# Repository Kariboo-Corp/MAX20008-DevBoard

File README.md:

This repo contains my work on the MAX20008 buck converter. The *Gerbers* folder contains the fabrication outputs, the *BOM+CPL* folder contains the BOM and CPL. 

## Component Dimensioning & Notes on PCB design

## Power supply : MAX 20008 

 In the board dimensioning file from the V1 MUAV Board I estimated that the eventual current draw of the MUAV board would be at least 6A (generous estimate).  I chose the MAX20008 buck converter, rated for 8A RMS. Here i detail the steps i took to dimension the different components . 

### RFOSC : 

using a Lower Fosc = lower temp increase, i chose fosc = 250Khz

with Fosc in kHz and Rosc in kohm 

We choose FOSC = 250kHz , RFOSC= 120 kohm soit 110kohm (E96) -> fosc = 243kHz

### power inductor 

Lmin1: we take Vin = 22.2V (nominal batt voltage)
m=0,15
Lmin1 = 6.5µH \\
Lmin2 = 11.1µH \\
Lmin = 6.5µH \\
Lmax = 6.8µH \\ 

we choose Lnom = 8.2µH, IMAX =8A, ISAT = 10A  : SRP1265C-100M : ISAT = 20A, Irms = 12A, L =10µF (no 8.2 µH available at this time)

### Input capacitor : 

Cin = 4.7µF minimum, capacitors used :GRT188R6YA475KE13 , LCSC part nb : C711100
Cbyp = 100nF, GRT188R6YA475KE13 type from murata , LCSC part nb : C85960

Celec = 47µF,  nichicon low esr 250mohm, LCSC part nb: C473201 

Iload(max) = 8A tehrefore Irms = 4A . Input cap should exhibit less than 10°c rise in temp at rms input current

Use low ESR cap 

### Output capacitor : 

we take DeltaV max = 50mV, Delta I = 2A,  fc = 10KHz 

Cout = 63µF min, we take  Cout= 100µF part nb =  GRM32ER61A107ME20L

### Compensation circuitry : 

GEA = 780µS, REA = 1.5MOhm   CHECK VALUES!!! -> DNP on PCB for now

We dimension RC = 8.8K, 
             CC = 39nF, 
             CF= 9nF 

### Reverse polarity protection: 

I added a  SB1060L schottky diode in series with Vin +, 
Forward voltage = 0. 55V , rated 10A . TO 277B package

JLCPCB part nb: C2929649

## Board Build

4 Layer board to emulate the final design's temperature caracteristics. 

The board is 50*72mm. Output is on two banana Jacks. Voltage input is on two solder/TH pads.  

Inductor current can be probed by placing a wire between these pads:

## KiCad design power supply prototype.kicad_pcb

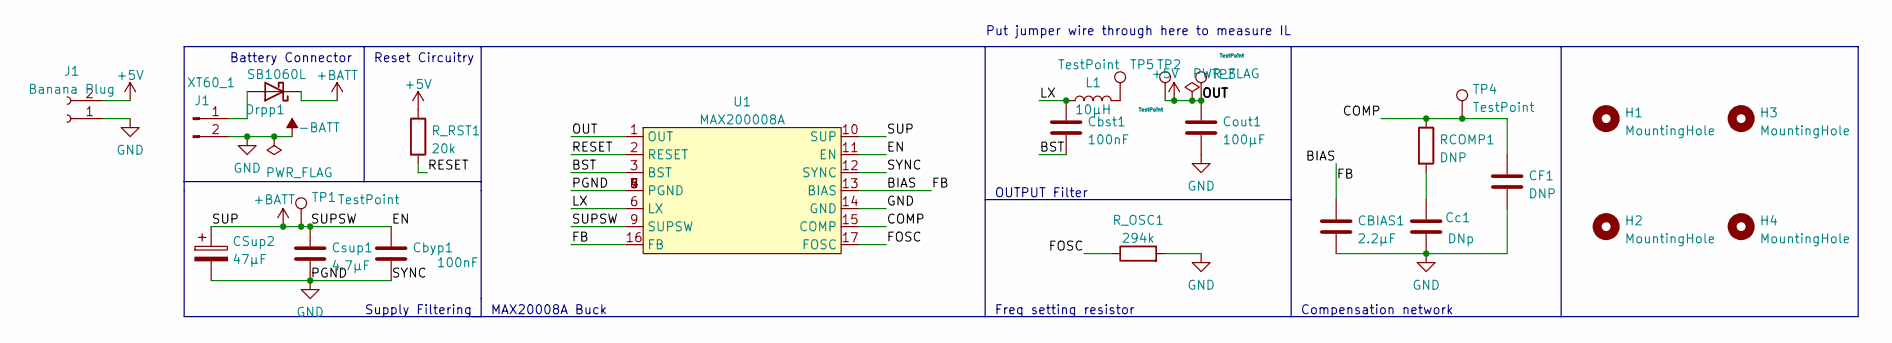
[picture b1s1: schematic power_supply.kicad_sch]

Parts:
CBIAS1: 2.2µF; C_0603_1608Metric_Pad1.08x0.95mm_HandSolder
CF1: DNP; C_0603_1608Metric_Pad1.08x0.95mm_HandSolder
CSup2: 47µF; CP_Elec_10x10.5; Part nb EEHZC1V470V
Cbst1: 100nF; C_0603_1608Metric_Pad1.08x0.95mm_HandSolder; part nb GCM188R71H104KA57D
Cbyp1: 100nF; C_0603_1608Metric_Pad1.08x0.95mm_HandSolder
Cc1: DNp; C_0603_1608Metric_Pad1.08x0.95mm_HandSolder
Cout1: 100µF; C_1210_3225Metric; part nb GRM32ER61A107ME20L
Csup1: 4.7µF; C_0603_1608Metric_Pad1.08x0.95mm_HandSolder
Drpp1: SB1060L; TO_277B
H1, H2, H3, H4: MountingHole; MountingHole_4.3mm_M4
J1: Banana Plug; Banana_Jack_2Pin
L1: 10µH; SRP1265C; Part nb EEHZA1E470V
RCOMP1: DNP; R_0603_1608Metric_Pad0.98x0.95mm_HandSolder
R_OSC1: 294k; R_0603_1608Metric_Pad0.98x0.95mm_HandSolder
R_RST1: 20k; R_0603_1608Metric_Pad0.98x0.95mm_HandSolder
TP1, TP2, TP3, TP4, TP5: TestPoint; TestPoint_THTPad_2.0x2.0mm_Drill1.0mm
U1: MAX200008A; MAX20008AFOB&slash_VY&plus_
XT60_1: J1; XT60 conn

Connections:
+5V: Cout1.1, J1.2, R_RST1.1, TP2.1, TP3.1, U1.1 (OUT); also elsewhere on the board
+BATT: CSup2.1, Cbyp1.1, Csup1.1, Drpp1.1 (K), TP1.1, U1.9 (SUPSW), U1.10 (SUP), U1.11 (EN)
-BATT: CBIAS1.2, CF1.2, CSup2.2, Cbyp1.2, Cc1.2, Cout1.2, Csup1.2, J1.1, R_OSC1.2, U1.4 (PGND), U1.5 (PGND), U1.7 (PGND), U1.8 (PGND), U1.12 (SYNC), U1.14 (GND), XT60_1.2; also elsewhere on the board
/power supply/BIAS: CBIAS1.1, U1.13 (BIAS), U1.16 (FB)
/power supply/BST: Cbst1.2, U1.3 (BST)
/power supply/COMP: CF1.1, RCOMP1.1, TP4.1, U1.15 (COMP)
/power supply/FOSC: R_OSC1.1, U1.17 (FOSC)
/power supply/LX: Cbst1.1, L1.1, U1.6 (LX)
/power supply/RESET: R_RST1.2, U1.2 (RESET)
unnamed: Cc1.1, RCOMP1.2
unnamed: Drpp1.2 (A), XT60_1.1
unnamed: L1.2, TP5.1

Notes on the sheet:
Freq setting resistor
OUTPUT Filter
Compensation network
Supply Filtering
Put jumper wire through here to measure IL
Reset Circuitry
Battery Connector
MAX20008A Buck

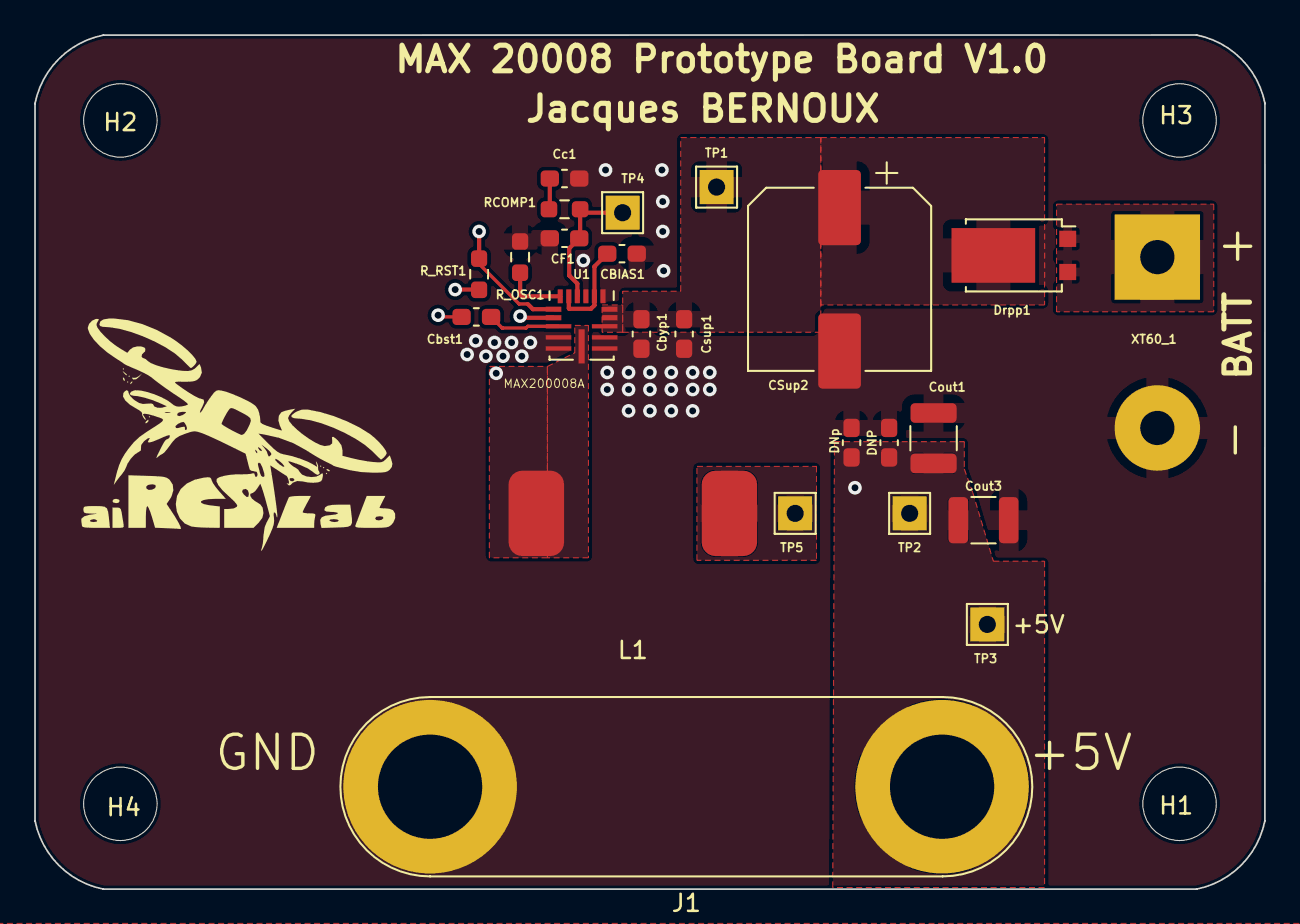
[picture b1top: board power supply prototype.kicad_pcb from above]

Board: 4 copper layers, 72.0 x 50.0 mm, 28 parts (0 on the bottom side), 12 nets.

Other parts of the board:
Cout3: DNP; C_1210_3225Metric
DNP: C_0603_1608Metric_Pad1.08x0.95mm_HandSolder
DNp: C_0603_1608Metric_Pad1.08x0.95mm_HandSolder

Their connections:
+5V: Cout3.1, DNP.1, DNp.1; also elsewhere on the board
-BATT: Cout3.2, DNP.2, DNp.2; also elsewhere on the board

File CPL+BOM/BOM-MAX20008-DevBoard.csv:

Column1;Column2;Column3;Column4
Comment;Designator;Footprint;LCSC Part #
2.2µF 50V  Unpolarized capacitor;CBIAS1;0603;C408135
100nF 50V Unpolarized capacitor;Cbst1,  Cbyp1;0603;C85960
DNP Unpolarized capacitor;Cc1;0603;DNP
DNP Unpolarized capacitor;CF1;0603;DNP
100µF 5V Low ESR Unpolarized capacitor;Cout1;1210;C84455
4.7µF 35 V low ESR Unpolarized capacitor;Csup1;0603;C711100
47µF low ESR 35V  Polarized capacitor;CSup2;CP_Elec_10x10.5;C473201
MountingHol;H1,H2,H3,H4;MountingHole_4.3mm_M4;DNP
Banana Plug ;J1;Banana_Jack_2Pin;DNP
10µH 18A  Inductor;L1;SRP1265C;DNP
294k Resistor;R_OSC1;0603;C13177
20k Resistor;R_RST1;0603;C22173
DNP Resistor;RCOMP1;0603;DNP
TestPoint : Pin Header;TP1,TP2,TP3,TP4,TP5;TestPoint_THTPad_2.0x2.0mm_Drill1.0mm;C492400
2 Pad connector;XT60_1;XT60 conn;DNP
SB1060L;Drpp1;TO277B;C2929649

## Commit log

2023-02-09 V0_proto
2023-02-09 Added README
2023-02-09 readme
2023-02-10 MAX20008 dev board update
    Added reverse polarity protection diode on the input.
